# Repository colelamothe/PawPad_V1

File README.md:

# PawPad_V1
Paw shaped QMK compatible macro pad

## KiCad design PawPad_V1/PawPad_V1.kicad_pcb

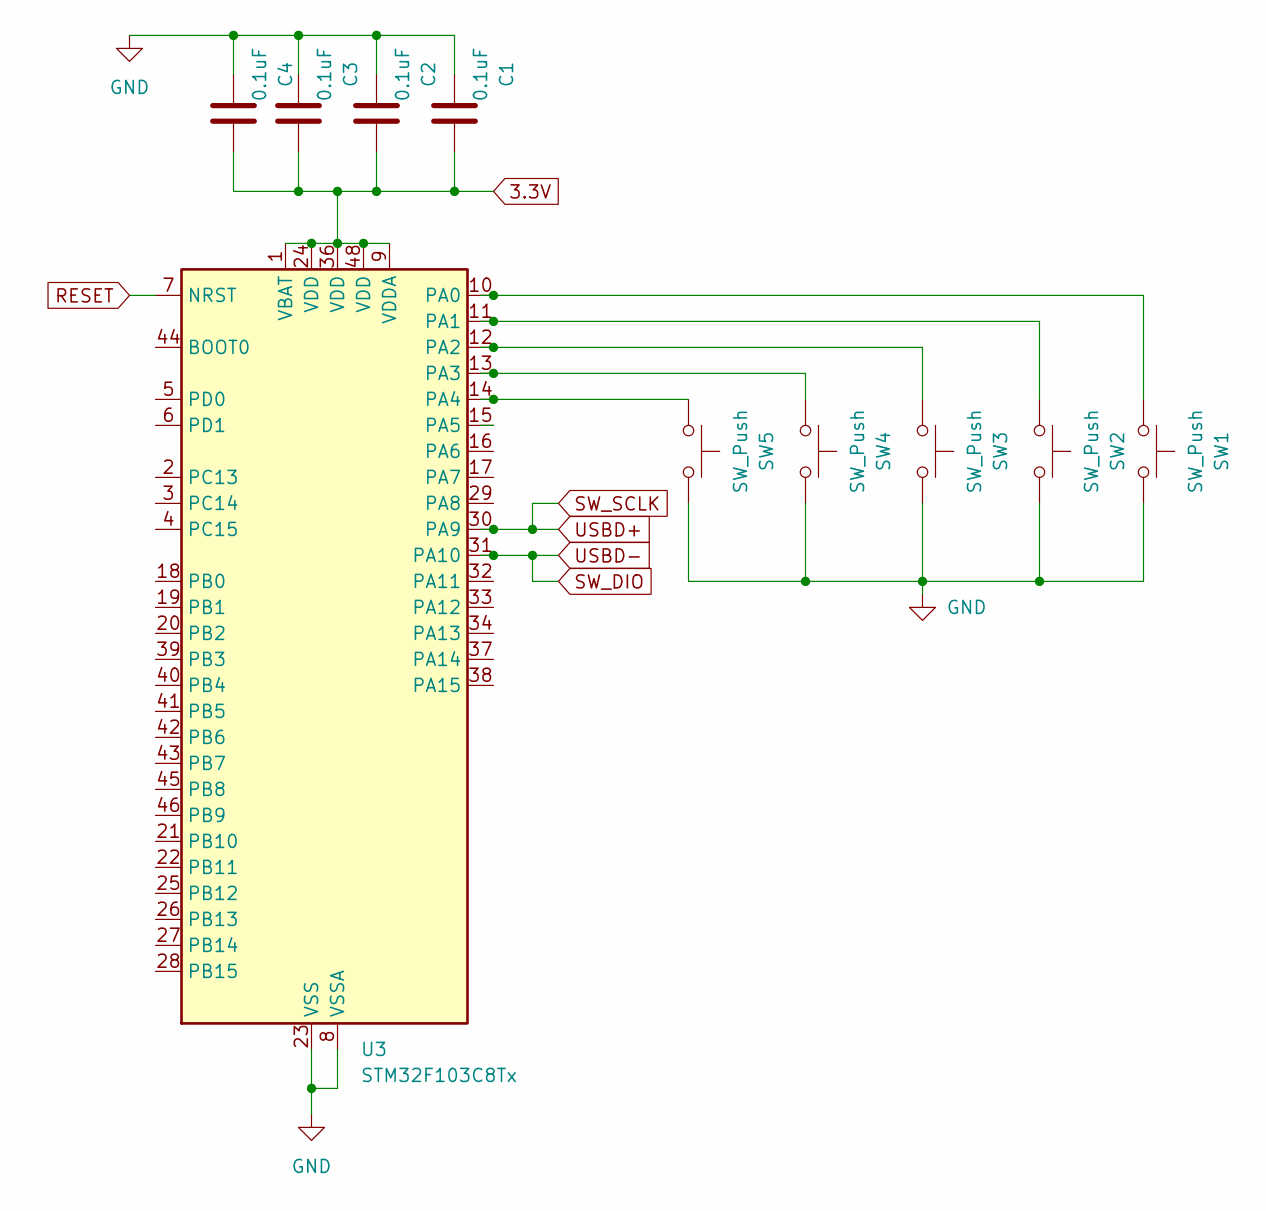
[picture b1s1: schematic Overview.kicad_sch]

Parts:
C1, C2, C3, C4: 0.1uF; C_0805_2012Metric_Pad1.18x1.45mm_HandSolder
SW1, SW2, SW3, SW4, SW5: SW_Push; Keyswitch Socket
U3: STM32F103C8Tx; LQFP-48_7x7mm_P0.5mm

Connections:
3.3V: C1.1, C2.2, C3.2, C4.2, U3.1 (VBAT), U3.9 (VDDA), U3.24 (VDD), U3.36 (VDD), U3.48 (VDD); also elsewhere on the board
GND: C1.2, C2.1, C3.1, C4.1, SW1.2, SW2.2, SW3.2, SW4.2, SW5.2, U3.8 (VSSA), U3.23 (VSS), U3.35 (VSS), U3.47 (VSS); also elsewhere on the board
unnamed: SW1.1, U3.10 (PA0)
unnamed: SW2.1, U3.11 (PA1)
unnamed: SW3.1, U3.12 (PA2)
unnamed: SW4.1, U3.13 (PA3)
unnamed: SW5.1, U3.14 (PA4)
RESET: U3.7 (NRST); also elsewhere on the board
SW_DIO: U3.31 (PA10); also elsewhere on the board
SW_SCLK: U3.30 (PA9); also elsewhere on the board

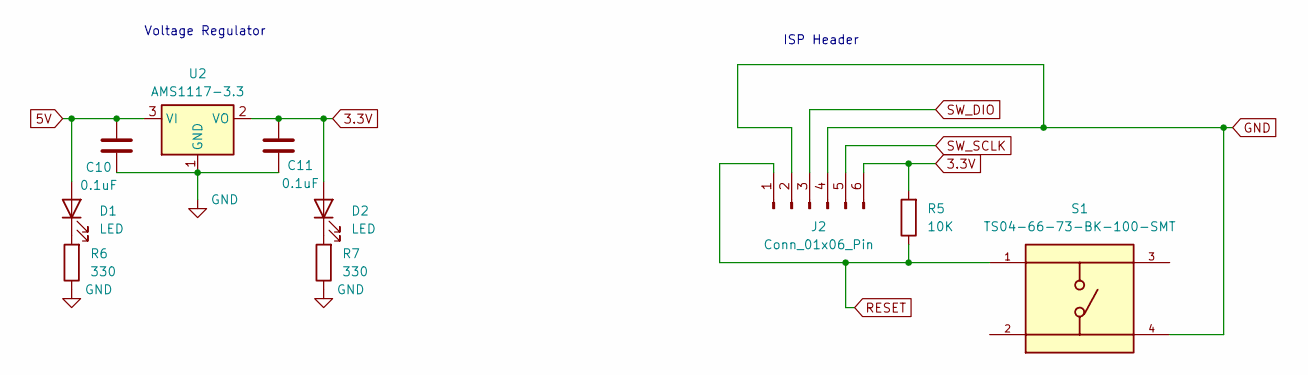
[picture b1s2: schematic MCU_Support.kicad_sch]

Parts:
C10, C11: 0.1uF; C_0805_2012Metric_Pad1.18x1.45mm_HandSolder
D1, D2: LED; LED_0603_1608Metric_Pad1.05x0.95mm_HandSolder
J2: Conn_01x06_Pin; PinHeader_2x03_P2.54mm_Vertical
R5: 10K; R_1206_3216Metric_Pad1.30x1.75mm_HandSolder
R6, R7: 330; R_1206_3216Metric_Pad1.30x1.75mm_HandSolder
S1: TS04-66-73-BK-100-SMT; SW_TS04-66-73-BK-100-SMT; PARTREV 1.0
U2: AMS1117-3.3; SOT-223-3_TabPin2

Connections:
3.3V: C11.1, D2.2 (A), J2.6, R5.2, U2.2 (VO); also elsewhere on the board
5V: C10.1, D1.2 (A), U2.3 (VI); also elsewhere on the board
GND: C10.2, C11.2, J2.2, J2.4, R6.1, R7.1, S1.4, U2.1 (GND); also elsewhere on the board
unnamed: D1.1 (K), R6.2
unnamed: D2.1 (K), R7.2
RESET: J2.1, R5.1, S1.1; also elsewhere on the board
SW_DIO: J2.3; also elsewhere on the board
SW_SCLK: J2.5; also elsewhere on the board

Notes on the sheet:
Voltage Regulator
ISP Header

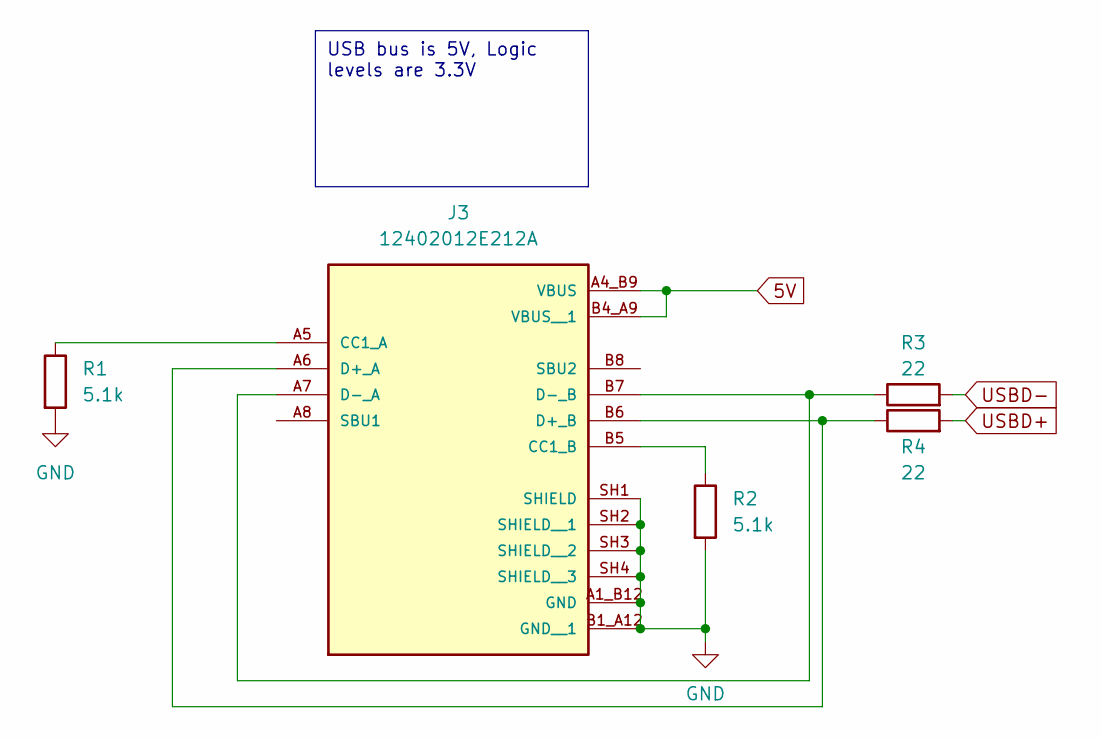
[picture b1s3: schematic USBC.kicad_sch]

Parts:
J3: 12402012E212A; USBC_AMPHENOL_12402012E212A; PARTREV 4
R1, R2: 5.1k; R_1206_3216Metric_Pad1.30x1.75mm_HandSolder
R3, R4: 22; R_1206_3216Metric_Pad1.30x1.75mm_HandSolder

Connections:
5V: J3.A4_B9 (VBUS), J3.B4_A9 (VBUS__1); also elsewhere on the board
GND: J3.A1_B12 (GND), J3.B1_A12 (GND__1), J3.SH1 (SHIELD), J3.SH2 (SHIELD__1), J3.SH3 (SHIELD__2), J3.SH4 (SHIELD__3), R1.2, R2.2; also elsewhere on the board
unnamed: J3.A5 (CC1_A), R1.1
unnamed: J3.B5 (CC1_B), R2.1
unnamed: J3.A6 (D+_A), J3.B6 (D+_B), R4.1
unnamed: J3.A7 (D-_A), J3.B7 (D-_B), R3.1
SW_DIO: R3.2; also elsewhere on the board
SW_SCLK: R4.2; also elsewhere on the board

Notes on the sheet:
USB bus is 5V, Logic levels are 3.3V

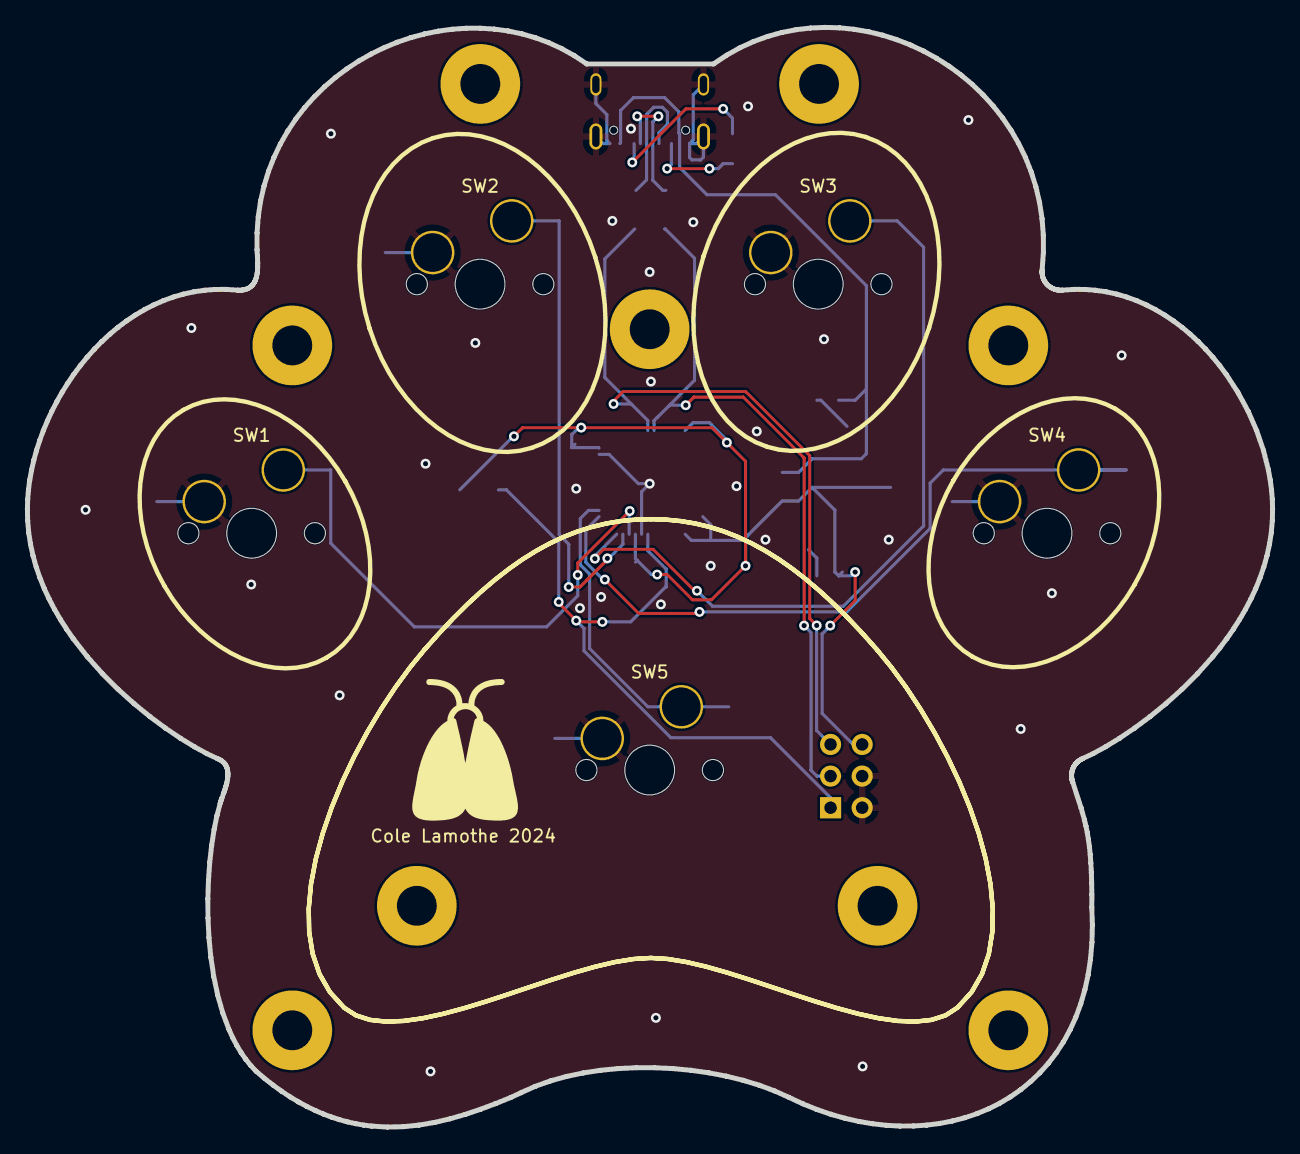
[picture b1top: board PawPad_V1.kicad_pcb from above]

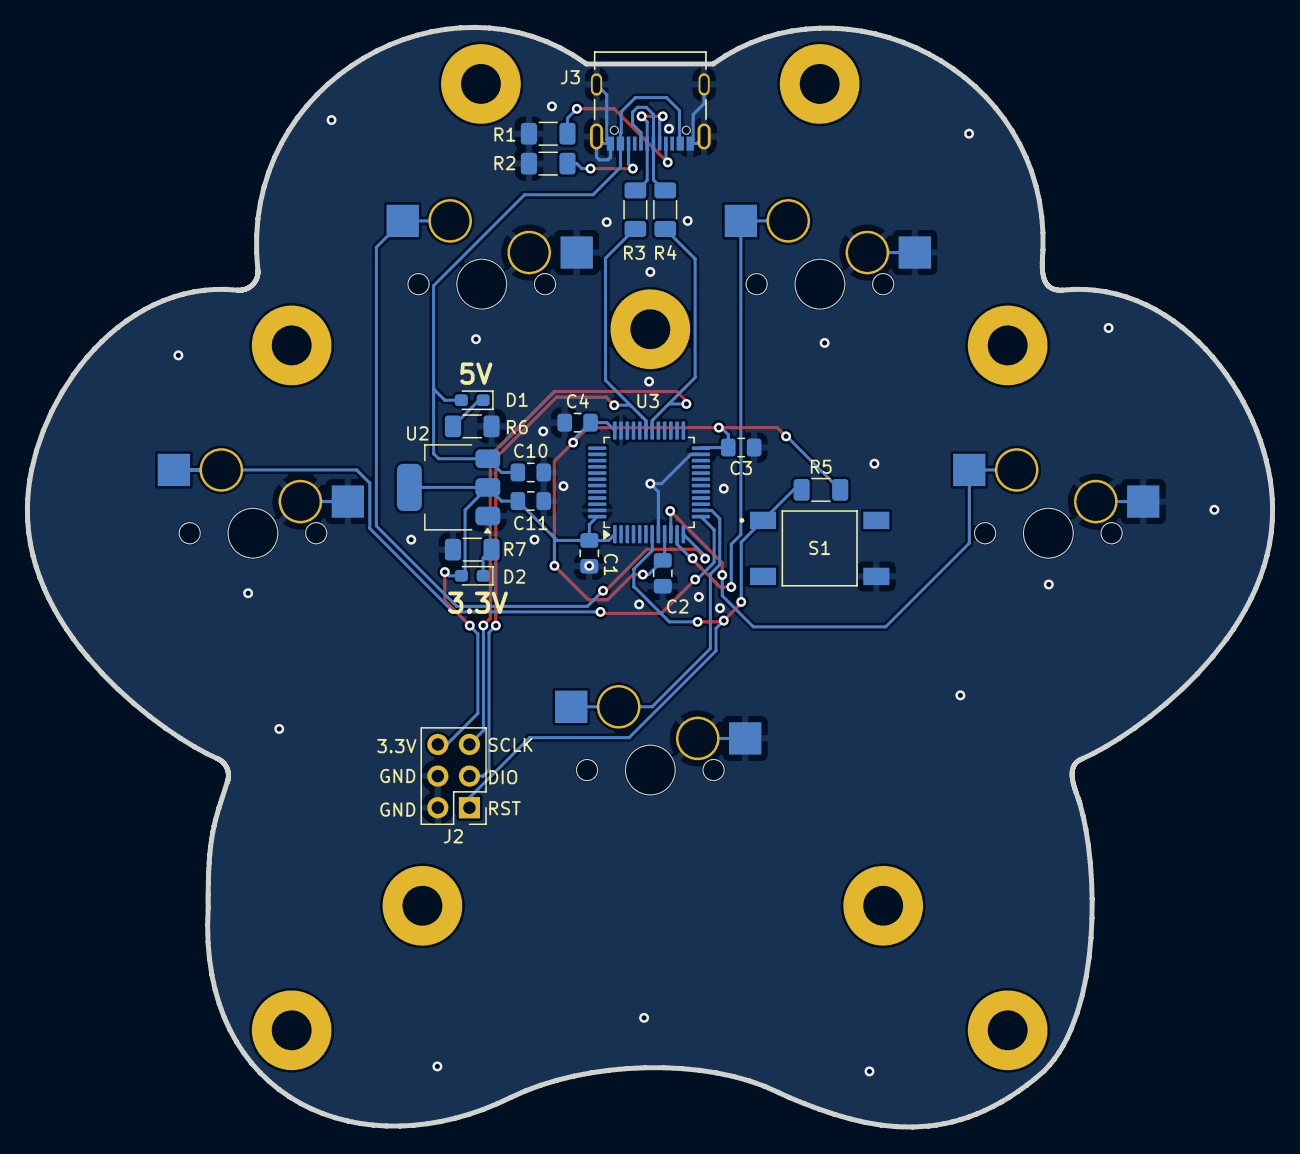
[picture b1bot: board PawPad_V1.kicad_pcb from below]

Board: 2 copper layers, 100.0 x 88.3 mm, 25 parts (20 on the bottom side), 17 nets.

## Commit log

2024-06-22 Add files via upload
    Initial commit of board for group review
